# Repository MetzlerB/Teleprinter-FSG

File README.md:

# Teleprinter-FSG
## Description 
---
This is a project that tries to emulate the FSG of the old phone network.
Without a FSG it is not possible to operate a teleprinter, at least not the old ones.
The goal of the project is to establish communication between a PC and the teleprinter and 
also between two separate teleprinter.

This project does not only provide the code for the uC, but also the files for the hardware side.
We know that there is already a project, called the iTelex, but this one is way to complicated and not 
really hacker friendly. (Also the hardware is way too expensive)

We want to provide an easy to use, cheap and hackable solution. 

We started this project as a university assignment and are currently working with three people on it. 
For us it is a learning experience so don't be too harsh.

Due to being a university assignment we can't allow any participants until we handed it in, so please stay put.

## Structure
---
#### Software:
All software related parts of the project can be found in "code/"

#### Hardware:
All hardware related parts of the project can be found in "KiCad/"

## Status
--- 
non-working developing state

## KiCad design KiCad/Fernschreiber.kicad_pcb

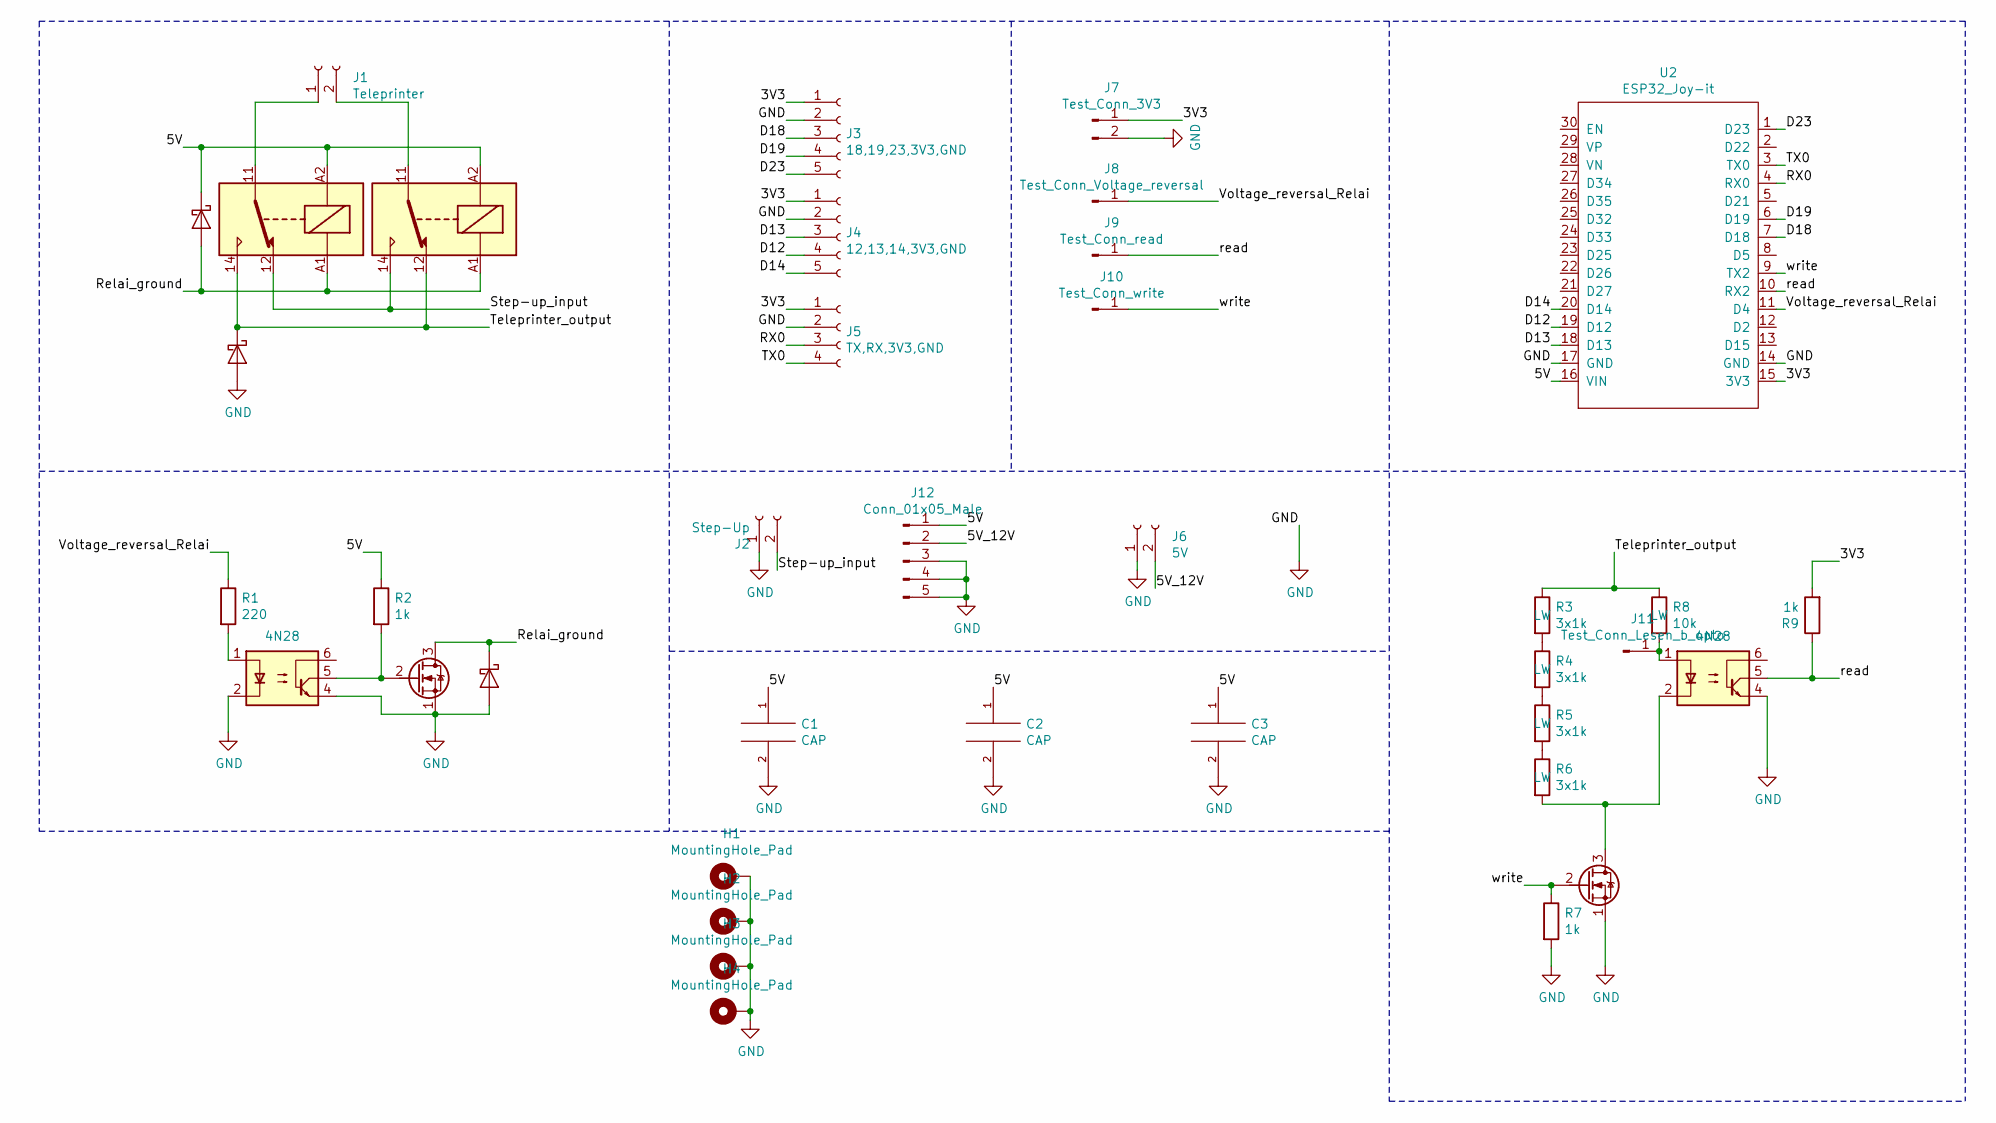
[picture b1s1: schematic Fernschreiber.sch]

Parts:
C1, C2, C3: CAP; CP_Radial_D8.0mm_P3.50mm
D1, D2, D3: 1N5711; D_DO-201AE_P15.24mm_Horizontal
H1, H2, H3, H4: MountingHole_Pad; Hole
J1: Teleprinter; DECA MB310-500M02 Schraubklemmblock
J2: Step-Up; DECA MB310-500M02 Schraubklemmblock
J3: 18,19,23,3V3,GND; PinHeader_1x05_P2.54mm_Vertical
J4: 12,13,14,3V3,GND; PinHeader_1x05_P2.54mm_Vertical
J5: TX,RX,3V3,GND; PinHeader_1x04_P2.54mm_Vertical
J6: 5V; DECA MB310-500M02 Schraubklemmblock
J7: Test_Conn_3V3; PinHeader_1x02_P2.54mm_Vertical
J8: Test_Conn_Voltage_reversal; PinHeader_1x01_P2.54mm_Vertical
J9: Test_Conn_read; PinHeader_1x01_P2.54mm_Vertical
J10: Test_Conn_write; PinHeader_1x01_P2.54mm_Vertical
J11: Test_Conn_Lesen_b_opto; PinHeader_1x01_P2.54mm_Vertical
J12: Conn_01x05_Male; stepdown
K1, K2: FINDER-40.41; BPM1-SS-105L
Q1, Q2: Q_NMOS_SGD; FQP30N06L
R1: 220; R_Axial_DIN0411_L9.9mm_D3.6mm_P12.70mm_Horizontal
R2, R7, R9: 1k; R_Axial_DIN0411_L9.9mm_D3.6mm_P12.70mm_Horizontal
R3, R4, R5, R6: 3x1k; 3X1k_Parallel
R8: 10k; R_Axial_DIN0414_L11.9mm_D4.5mm_P15.24mm_Horizontal
U1, U3: 4N28; IC-Fassung-6pol
U2: ESP32_Joy-it

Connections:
/3V3: J3.1, J4.1, J5.1, J7.1, R9.2, U2.15 (3V3)
/5V: C1.1, C2.1, C3.1, D1.1 (K), J12.1, K1.A2, K2.A2, R2.1, U2.16 (VIN)
/5V_12V: J6.2, J12.2
/D12: J4.4, U2.19 (D12)
/D13: J4.3, U2.18 (D13)
/D14: J4.5, U2.20 (D14)
/D18: J3.3, U2.7 (D18)
/D19: J3.4, U2.6 (D19)
/D23: J3.5, U2.1 (D23)
/RX0: J5.3, U2.4 (RX0)
/Relai_ground: D1.2 (A), D3.1 (K), K1.A1, K2.A1, Q1.3 (D)
/Step-up_input: J2.2, K1.12, K2.14
/TX0: J5.4, U2.3 (TX0)
/Teleprinter_output: D2.1 (K), K1.14, K2.12, R3.1, R8.1
/Voltage_reversal_Relai: J8.1, R1.1, U2.11 (D4)
/read: J9.1, R9.1, U2.10 (RX2), U3.5
/write: J10.1, Q2.2 (G), R7.1, U2.9 (TX2)
GND: C1.2, C2.2, C3.2, D2.2 (A), D3.2 (A), H1.1, H2.1, H3.1, H4.1, J2.1, J3.2, J4.2, J5.2, J6.1, J7.2, J12.3, J12.4, J12.5, Q1.1 (S), Q2.1 (S), R7.2, U1.2, U1.4, U2.14 (GND), U2.17 (GND), U3.4
unnamed: J1.1, K1.11
unnamed: J1.2, K2.11
unnamed: J11.1, R8.2, U3.1
unnamed: Q1.2 (G), R2.2, U1.5
unnamed: Q2.3 (D), R6.2, U3.2
unnamed: R1.2, U1.1
unnamed: R3.2, R4.1
unnamed: R4.2, R5.1
unnamed: R5.2, R6.1

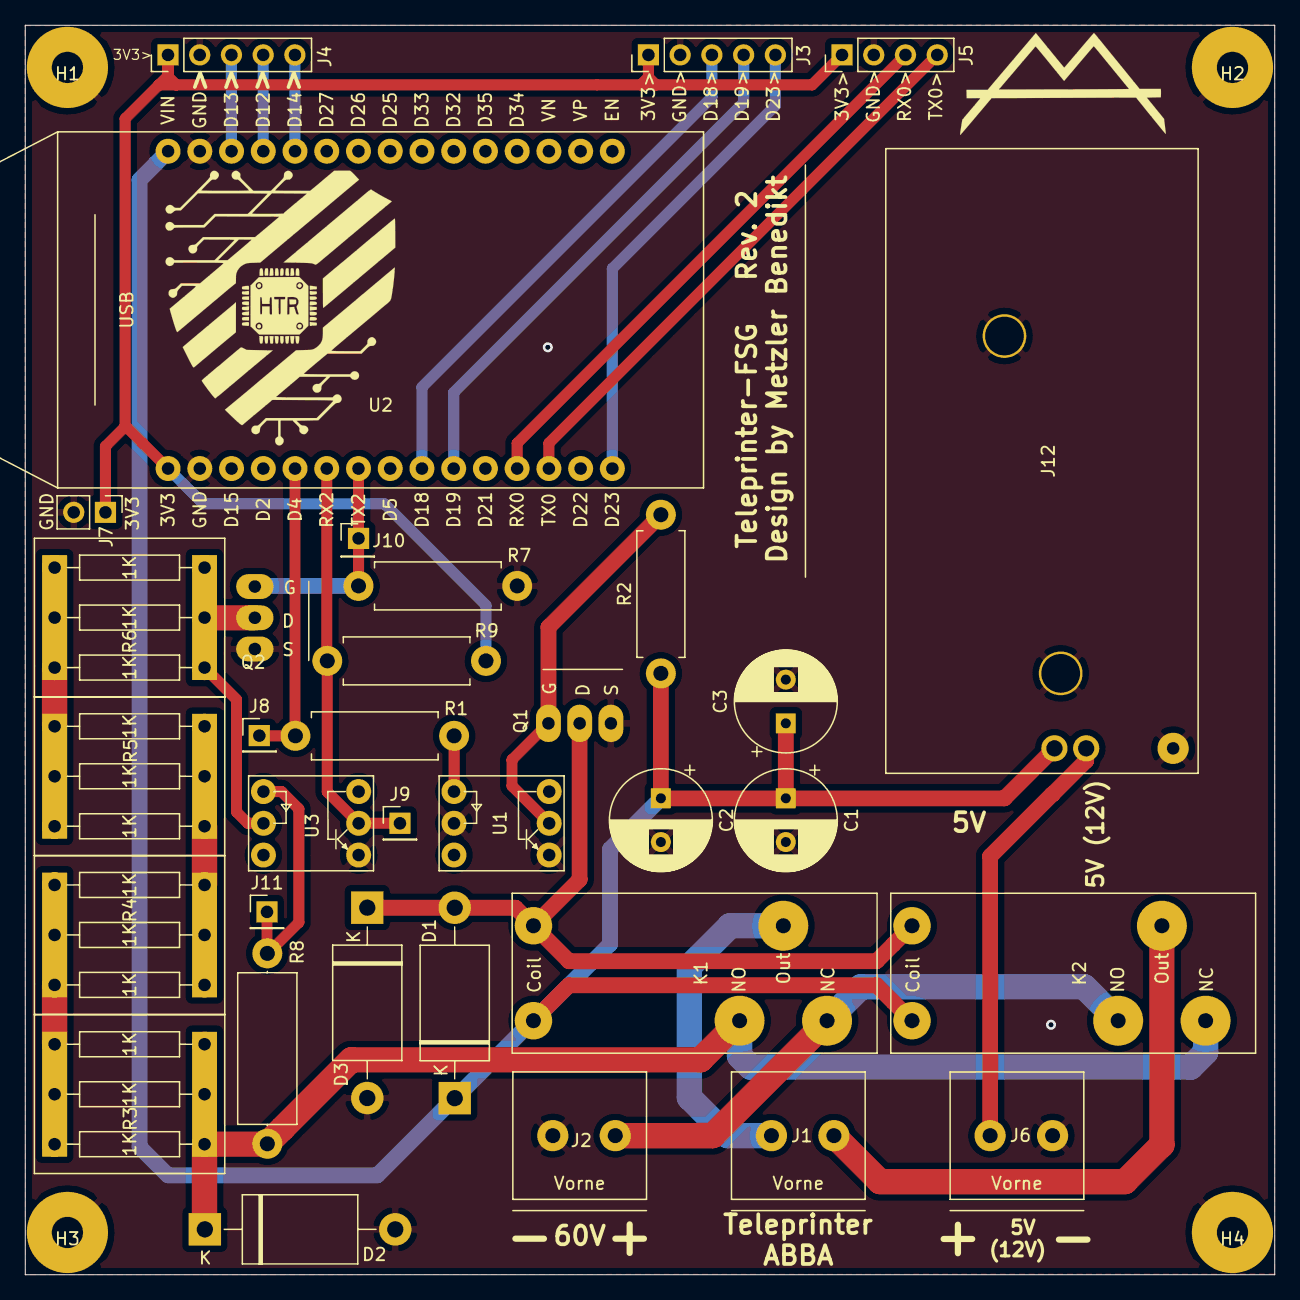
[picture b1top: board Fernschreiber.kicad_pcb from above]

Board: 2 copper layers, 100.0 x 100.0 mm, 38 parts (0 on the bottom side), 27 nets.

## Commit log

2020-02-29 added gitignore
2020-02-29 init commit
2020-02-29 added travis build file
2020-03-01 added commend for clarification
2020-03-01 edit debug output for easier understanding
2020-04-25 Changed file name of the original program to old_main old_main is only a look up for the new program and should not be copied
2020-04-25 Modified file to not include old_main
2020-04-25 New main with little test programm and getMillisDifference function
2020-08-31 PCB file KiCad
2020-08-31 KiCad lib file
2020-08-31 KiCad network file
2020-08-31 Footprint Power Resistor
2020-08-31 Footprint Terminal block header
2020-08-31 Fottprint ESP32_Joy
2020-08-31 Footprint IC socket
2020-08-31 Footprint Relai
2020-08-31 Footprint linear regulator 3.3V
2020-08-31 Footprint Lineaar regulator 5V
2020-08-31 Footprint Mosfet
2020-08-31 KiCad file
2020-08-31 KiCad curcuit diagram
2020-08-31 Kicad lib table
2020-09-01 moved everything code related into a Folder named code
2020-09-01 moved some more files
2020-09-01 Renamed folder to KiCad
2020-09-01 created general README
2020-09-01 created empty README for "code" and "KiCad"
2020-10-08 added sequenzdiagramm that was created by someone else [HTR]
2020-10-23 Modified footprint-lib (relai and esp32) routing PCB (not finished yet)
2020-10-23 Modified Footprints, routing PCB(not finished yet)
2020-10-26 Finished routing PCB + updated Footprints + updated Symbols + updated Schematic + ordered PCB at JLCPCB
2020-12-11 Funktion_FSG_anbieten contains all needed functions of the FSG (contains also some nict to have functions)
2021-03-04 save latest kicad files (nothing chnaged)
2021-03-04 Changed old_main to main for testing, changed ini for testing
2021-03-04 Todo for changes for Schematic and PCB
2021-03-04 changed to main
2021-03-07 marked changes
2021-03-07 Changed schemetic removed powersupply changed opto read connection removed Diode 4 overall improved schemetic
2021-03-07 new netlist
2021-03-07 Rev.2 PCB
2021-03-07 Rework footprints
2021-03-11 added Step_down Footprint to local lib
2021-03-12 Updated PCB
2021-03-22 changed connector Position
2021-03-22 generated Gerber files for order
2021-03-22 added selfdesigned stepdown to repo
2021-03-22 Added 3D models to every component of the teleprinter
2021-03-22 Added 3d components to the stepdown, and also added the stepdown to the teleprinter
2021-03-22 removed all temporary file and added .gitignore + moved the gerber files to a zip file (gerber shouldn't normally be in a git repository)
2021-03-23 Exported 3D PCB Version
